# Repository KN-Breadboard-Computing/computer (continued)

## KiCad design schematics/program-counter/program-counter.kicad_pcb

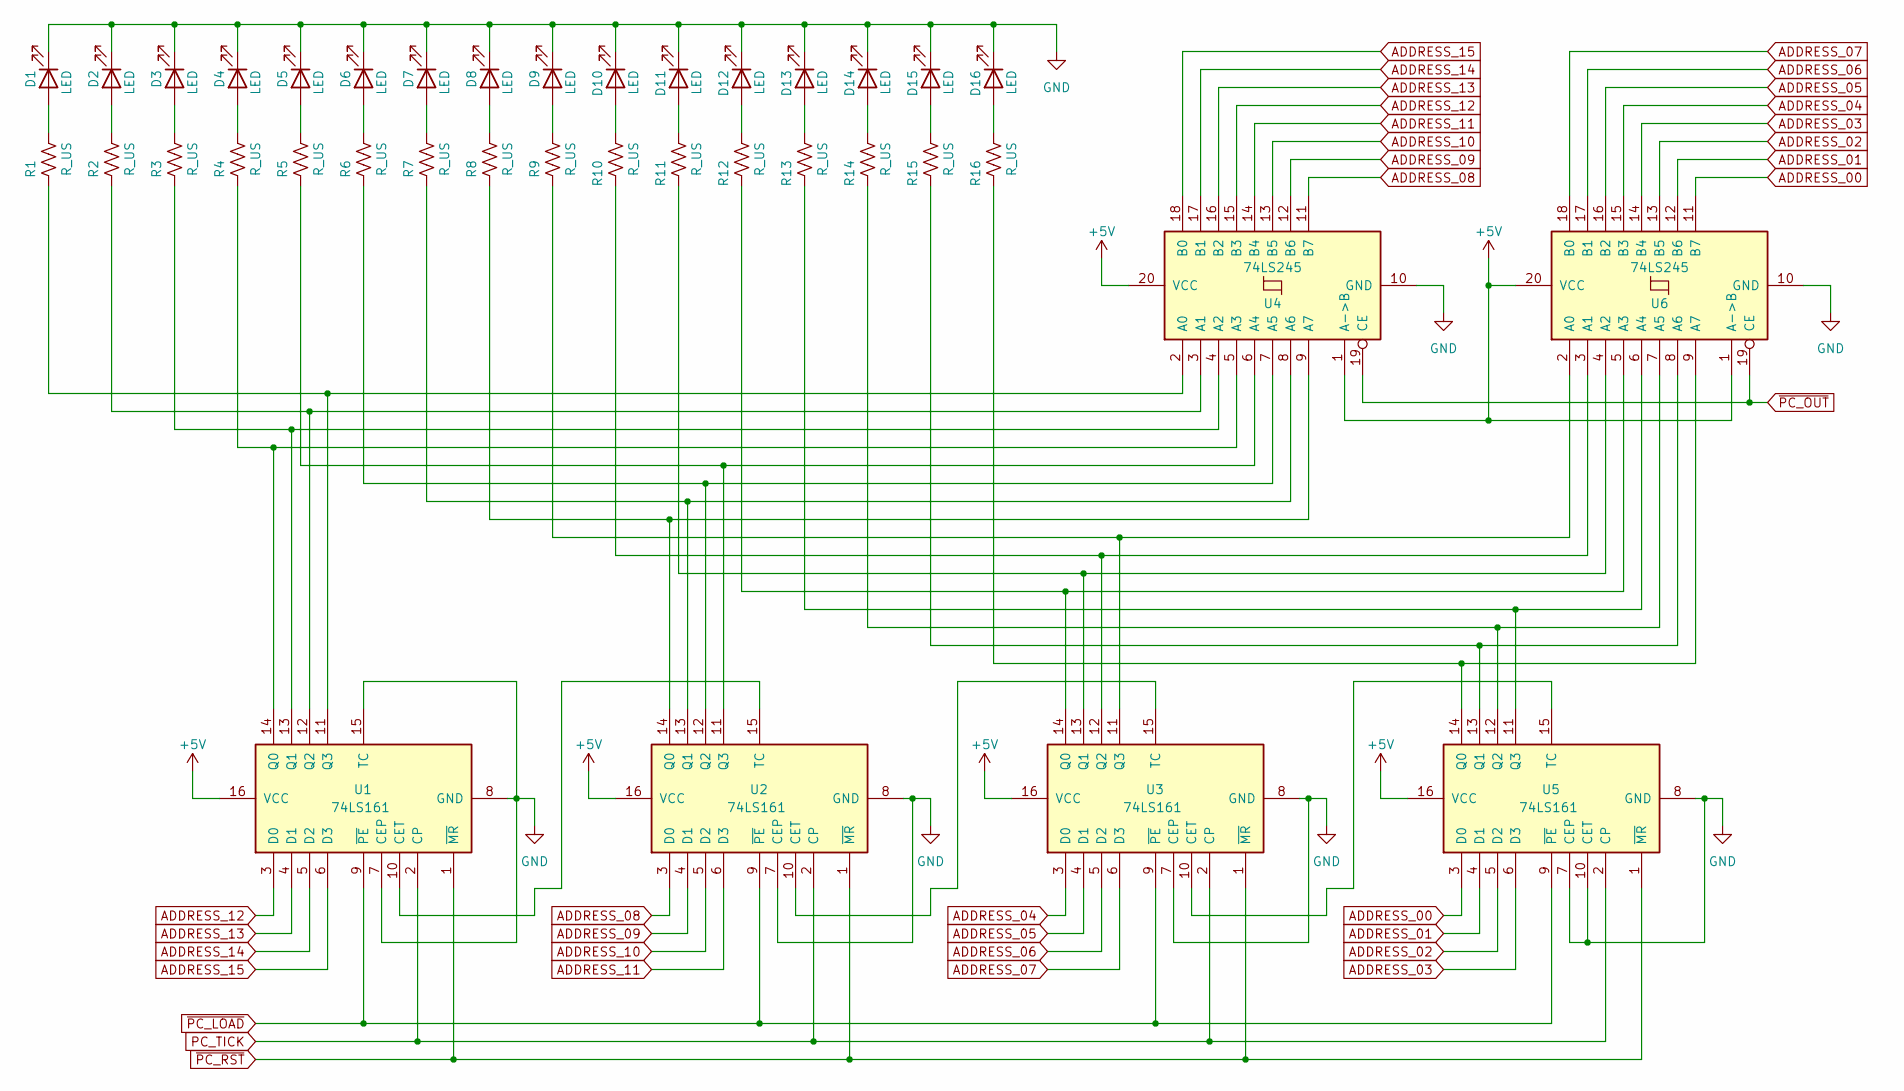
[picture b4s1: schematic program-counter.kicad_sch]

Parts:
D1, D2, D3, D4, D5, D6, D7, D8, D9, D10, D11, D12, D13, D14, D15, D16: LED; LED_D3.0mm
R1, R2, R3, R4, R5, R6, R7, R8, R9, R10, R11, R12, R13, R14, R15, R16: R_US; R_Axial_DIN0207_L6.3mm_D2.5mm_P10.16mm_Horizontal
U1, U2, U3, U5: 74LS161; DIP-16_W7.62mm_LongPads
U4, U6: 74LS245; DIP-20_W7.62mm_LongPads

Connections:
+5V: U1.16 (VCC), U2.16 (VCC), U3.16 (VCC), U4.1 (A->B), U4.20 (VCC), U5.16 (VCC), U6.1 (A->B), U6.20 (VCC)
ADDRESS_00: U5.3 (D0), U6.11 (B7)
ADDRESS_01: U5.4 (D1), U6.12 (B6)
ADDRESS_02: U5.5 (D2), U6.13 (B5)
ADDRESS_03: U5.6 (D3), U6.14 (B4)
ADDRESS_04: U3.3 (D0), U6.15 (B3)
ADDRESS_05: U3.4 (D1), U6.16 (B2)
ADDRESS_06: U3.5 (D2), U6.17 (B1)
ADDRESS_07: U3.6 (D3), U6.18 (B0)
ADDRESS_08: U2.3 (D0), U4.11 (B7)
ADDRESS_09: U2.4 (D1), U4.12 (B6)
ADDRESS_10: U2.5 (D2), U4.13 (B5)
ADDRESS_11: U2.6 (D3), U4.14 (B4)
ADDRESS_12: U1.3 (D0), U4.15 (B3)
ADDRESS_13: U1.4 (D1), U4.16 (B2)
ADDRESS_14: U1.5 (D2), U4.17 (B1)
ADDRESS_15: U1.6 (D3), U4.18 (B0)
GND: D1.1 (K), D2.1 (K), D3.1 (K), D4.1 (K), D5.1 (K), D6.1 (K), D7.1 (K), D8.1 (K), D9.1 (K), D10.1 (K), D11.1 (K), D12.1 (K), D13.1 (K), D14.1 (K), D15.1 (K), D16.1 (K), U1.7 (CEP), U1.8 (GND), U1.15 (TC), U2.7 (CEP), U2.8 (GND), U3.7 (CEP), U3.8 (GND), U4.10 (GND), U5.7 (CEP), U5.8 (GND), U5.10 (CET), U6.10 (GND)
unnamed: D1.2 (A), R1.2
unnamed: D2.2 (A), R2.2
unnamed: D3.2 (A), R3.2
unnamed: D4.2 (A), R4.2
unnamed: D5.2 (A), R5.2
unnamed: D6.2 (A), R6.2
unnamed: D7.2 (A), R7.2
unnamed: D8.2 (A), R8.2
unnamed: D9.2 (A), R9.2
unnamed: D10.2 (A), R10.2
unnamed: D11.2 (A), R11.2
unnamed: D12.2 (A), R12.2
unnamed: D13.2 (A), R13.2
unnamed: D14.2 (A), R14.2
unnamed: D15.2 (A), R15.2
unnamed: D16.2 (A), R16.2
unnamed: U1.10 (CET), U2.15 (TC)
unnamed: R4.1, U1.14 (Q0), U4.5 (A3)
unnamed: R3.1, U1.13 (Q1), U4.4 (A2)
unnamed: R2.1, U1.12 (Q2), U4.3 (A1)
unnamed: R1.1, U1.11 (Q3), U4.2 (A0)
unnamed: U2.10 (CET), U3.15 (TC)
unnamed: R8.1, U2.14 (Q0), U4.9 (A7)
unnamed: R7.1, U2.13 (Q1), U4.8 (A6)
unnamed: R6.1, U2.12 (Q2), U4.7 (A5)
unnamed: R5.1, U2.11 (Q3), U4.6 (A4)
unnamed: U3.10 (CET), U5.15 (TC)
unnamed: R12.1, U3.14 (Q0), U6.5 (A3)
unnamed: R11.1, U3.13 (Q1), U6.4 (A2)
unnamed: R10.1, U3.12 (Q2), U6.3 (A1)
unnamed: R9.1, U3.11 (Q3), U6.2 (A0)
unnamed: R16.1, U5.14 (Q0), U6.9 (A7)
unnamed: R15.1, U5.13 (Q1), U6.8 (A6)
unnamed: R14.1, U5.12 (Q2), U6.7 (A5)
unnamed: R13.1, U5.11 (Q3), U6.6 (A4)
PC_INC: U1.2 (CP), U2.2 (CP), U3.2 (CP), U5.2 (CP)
~PC_LOAD: U1.9 (~PE), U2.9 (~PE), U3.9 (~PE), U5.9 (~PE)
~PC_OUT: U4.19 (CE), U6.19 (CE)
~PC_RST: U1.1 (~MR), U2.1 (~MR), U3.1 (~MR), U5.1 (~MR)

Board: 2 copper layers, 38 parts (0 on the bottom side), 57 nets, no tracks yet.

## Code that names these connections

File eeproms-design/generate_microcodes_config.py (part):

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        }

    def _alu_operation(self, code):
        self._signals['~ALU_OUT'] = 0
        for i in range(0, 5):
            self._signals[f'ALU_OPC_{i}'] = (code >> i) & 0x1
    
    def no_mcc_tick(self):
        self._signals['MCC_TICK'] = 0
        return self 

    def mcc_rst(self):
        self._signals['MCC_RST'] = 1

    def reg_to_bus(self, reg):
        assert reg in WORD_REGS or reg == REG_F or reg == REG_INT
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            self._signals[f'~REG_{reg}_PASS_DATA'] = 0

        if reg == REG_F:
            self._signals['~REG_F_OUT'] = 0

        if reg == REG_INT:
            self._signals['~INT_DATA_OUT'] = 0
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        return self

    def pc_out(self):
        self._signals['~PC_OUT'] = 0
        return self

    def pc_in(self):
        self._signals['~PC_LOAD'] = 0
        return self

    def pc_inc(self):
        self._signals['PC_TICK'] = 1
        return self

    def mar_in(self):
        self._signals['REG_MAR_LOAD'] = 1
        return self

    def ir_in(self):
        self._signals['REG_IR_LOAD'] = 1
        return self

    def mbr_in(self):
        self._signals['REG_MBR_LOAD'] = 1
        self._signals['~REG_MBR_USE_BUS'] = 0
        self._signals['REG_MBR_WORD_DIR'] = 1
        return self

    def mem_to_bus(self, zero_page=False, stack=False):
        self._signals['REG_MBR_WORD_DIR'] = 0
        self._signals['~MEM_OUT'] = 0
        self._signals['~REG_MBR_USE_BUS'] = 0
        self._signals['~ZERO_PAGE'] = 0 if zero_page else 1
        self._signals['MEM_PART'] = 1 if stack else 0
        return self

    def mem_to_mbr(self, zero_page=False, stack=False):
        self._signals['REG_MBR_LOAD'] = 1
        self._signals['~MEM_OUT'] = 0
        self._signals['~ZERO_PAGE'] = 0 if zero_page else 1
        self._signals['MEM_PART'] = 1 if stack else 0
        return self

    def mbr_to_mem(self, zero_page=False, stack=False):
        self._signals['~MEM_IN'] = 0
        self._signals['~ZERO_PAGE'] = 0 if zero_page else 1
        self._signals['MEM_PART'] = 1 if stack else 0
        return self
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            self._signals[f'REG_{dst}_LOAD'] = 1

            if dst == REG_MBR:
                self._signals['~REG_MBR_USE_BUS'] = 0

        return self

    def tmp_out(self):
        self._signals['~REG_TMPH_OUT'] = 0
        self._signals['~REG_TMPL_OUT'] = 0
        self._signals['REG_TMP_ADDRESS_DIR'] = 0
        self._signals['~REG_TMP_PASS_ADDRESS'] = 0
        return self

    def tmp_in(self):
        return self.reg_from_bus(REG_TL).reg_from_bus(REG_TH)

    def tmp_addr_in(self):
        self._signals['REG_TMPH_LOAD'] = 1
        self._signals['REG_TMPL_LOAD'] = 1
        self._signals['REG_TMP_ADDRESS_DIR'] = 1
        self._signals['~REG_TMP_PASS_ADDRESS'] = 0
        return self

    def stc_out(self):
        self._signals['~STC_OUT'] = 0
        return self

    def stc_dec(self):
        self._signals['STC_TICK'] = 1
        return self

    def stc_inc(self):
        self._signals['STC_TICK'] = 1
        self._signals['STC_MODE'] = 1
        return self

    def set_int_enable(self):
        self._signals['SET_INT_ENABLE'] = 1
        return self

    def rst_int_enable(self):
        self._signals['RST_INT_ENABLE'] = 1
        return self

    def int_addr_out(self):
        self._signals['~INT_ADDRESS_OUT'] = 1
        return self
    
    def int_data_out(self):
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        return self
    
    def select_boot_memory(self):
        self._signals['MEMORY_SELECTOR'] = 0
        return self

    def to_json(self):
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
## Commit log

2022-12-15 Created program counter project in logisim
2023-01-30 Added notes
2023-01-30 Changes to noets
2023-02-27 Programming EEPROMs - first version of signals
2023-04-07 Changes in eeproms code
2023-04-09 Deleted old and useless files
2023-04-09 Initial schematic projects
2023-07-06 Created almost all schematics
2023-07-06 Arduino code updates
2023-07-06 ReadMe update
2023-07-31 Directories refactor
2023-07-31 Script for eeproms programming. Implemented alu logic eeprom
2023-07-31 Named signal masks
2023-07-31 Base of architecture manual and arduino memory writer
2023-07-31 Corrected ALU schematic after diy pcb soldered
2023-07-31 Described flags
2023-07-31 Photo report - stage 1
2023-08-18 Implemented bus control
2023-08-21 Corrections after second diy pcb soldered
2023-08-22 Code for eeproms with basic instruction decoding
2023-08-22 Deleted pycache
2023-08-25 Control unit build
2023-10-04 Implemented signals visualization
2023-10-10 Changed signals visualisation
2023-10-24 New instructions tested
2023-11-20 Manual -> github pages
2023-11-26 Repo structure refactor
2023-11-26 Move instructions
2023-11-26 Created script for generating alu config
2023-11-27 Alu instructions
2023-12-12 Created a basic verilog project structure
2023-12-18 Renamed the verilog-project/ dir to verilog/
2023-12-18 Updated CMakeLists, integrated ctest
2023-12-18 Removed the temporary ALU, added a tristate buffer
2023-12-18 Signal definitions
2023-12-18 Created skeleton files for alu, cpu and control unit
2023-12-18 Added register
2023-12-18 Counter
2023-12-18 Added RAM (broken)
2023-12-18 Counter fix and more cpu
2023-12-18 Added a newline!
2023-12-18 Fixed cmake
2023-12-18 Fixed commas
2023-12-18 Created base for ALU
2023-12-19 Fixed alu, added tests for alu, added fixmes to ram
2023-12-19 Added examples
2023-12-19 Tests for counter
2023-12-19 ALU in CPU and changed parameter declarations
2023-12-20 Update instructions.json
    added missing HALT instruction
2023-12-21 Instructions have been completed
2023-12-21 Instruction json formatted
2023-12-21 Removed MUL2 operation
2024-01-15 Update generate_instructions_config.py
    naprawione
2024-01-15 Generated fresh config
2024-01-20 Added "depend-on-flag" field to instructions config and generated new one.
2024-02-13 [verilog] Fixed RAM, added Memory Unit
    - Write to RAM is triggered by write_enable going low, or a change in
    address (write_enable has to still be low). Changes in data, however,
    do not trigger anything
    - In Mem Unit MAR and MBR only store a new value on the rising edge of
    their respective signals. This means that 2 consecutive commands to
    load MAR/MBR will not work unless there is a assertion of thier load
2024-02-14 Rewritten tests for ALU, added .clang-format
2024-02-14 Added logging to ALU tests
2024-02-20 Made Control Unit process basic instructions
    - The ROM file generation that Control Unit needs to work is not
    included
    - Conditionals do not work
2024-02-22 Added microcodes generator
    - Only includes microcodes present in existing `config/microcodes.json`
    and `config/instructions.json`
    - There are some differences between hand written config and one
    generated by this script
    - Due to previous 2 points generated config is not included in this
    commit
2024-02-23 Added missing microcodes to the generator
    - Now all microcodes present in the `config/instructions.json` are
    generated
    - Increment and decrement microcodes are noops for now, due to lack of
    support in the ALU config (at least)
2024-02-24 Fixed EEPROM import and config paths
    - At least on my machine when run from `eeprom-design` directory
    everything is now imported properly
    - Config file paths are no longer hardcoded and can be now provided by
    users of EEPROM classes
2024-02-24 Added dump_eeproms.py utility
    - It generates and dumps the contents of EEPROMs into binary files
2024-02-26 Fixed stack related issues in microcode generator
    - Some microcodes that should have operated on the stack, did not
2024-02-26 Added more elaborate Control Unit tests
    - Now more instructions are tested
    - Probably all of them should be tested
    - And, too be fair hardcoding microdes into tests might not have been
    the smartest of ideas
2024-03-02 Added `branch` to instruction config
    - `branch.taken` - instruction that is executed if the branch is taken
    - `branch.not-taken` - instruction that is executed otherwise
2024-03-03 Added branch decoding EEPROM
2024-03-03 Added branches to Control Unit
    - Control Unit can now change its output depending on ALU flags and
    implement branching (via JMP and SKIP instructions)
2024-03-08 Added base for windowing using raylib
2024-03-08 Rewrote ALU, added ALU flags
    - Flags now work correctly
    - ALU more closely resembles its breadboard counterpart
    - Removed clock input (now it's mostly combinatorial logic)
2024-03-08 Added initial version of GPU verilator component
2024-03-09 Updated the simulator code to include a set_pixel function
2024-03-09 Changed the cursors in GPU to point to glyphs instead of individual pixels
2024-03-10 Added proof of concept GPU to the raylib simulation
2024-03-10 Added vertical and horizontal counters
2024-03-18 Added INT signals
    - Currently hard wired to 0, support from EEPROMs is needed to actually
    do something useful
2024-03-18 Added the TMP register
2024-04-02 Added glyph and color buffers to the GPU
2024-04-03 Font loading part 1
2024-04-03 Added a tool that converts a font image file to a binary accepted by the GPU
2024-04-03 Fixed the simulator, the GPU is still broken
2024-04-03 Added error handling if the GPU fails to open the Glyph data file
2024-04-04 Added a shift register module
2024-04-06 GPU now correctly loads the file, still displays nonsense though
2024-04-06 Changed the test for shift reg
2024-04-07 Working CPU
    - CPU now works, at least to pass a simple MOV-only test
2024-04-10 Added missing `cpu_adapter.sv`
2024-04-10 Added missing files
2024-04-10 Debug version of the simulator
2024-04-17 Made GPU render test graphics correctly
    - It now renders simple graphics in fonts/
    - I did not want to push this code, which I believe is very cursed
2024-04-18 Added modcounter
2024-04-18 Added tests for modcounter
2024-04-18 Moved resources to resources directory
2024-04-23 Added Clock wrapper and a scheduler to the simulator
2024-04-23 added ps2 keyboard raylib wrapper.
2024-04-23 fixed formatting.
2024-04-24 Added negative edge period to the clock and option to start from posedge, added missing imports to ps2.hpp
2024-04-29 Schematics and interrupts
2024-04-30 Diy pbcs photos
2024-05-03 Made CPU jump to ISR
    - Return from ISR does not work yet
2024-05-05 Improved details
2024-05-08 Added Set-Reset Latch
2024-05-08 Changed assert to be correct in struct Clock
2024-05-08 Fixed off by one problem in GPU
2024-05-08 Instructions moving interrupt data
2024-05-08 Int enable set/reset swapped
2024-05-09 Added full font
2024-05-14 Addded instructions triggering interrupts
2024-05-14 Sanitized the ps2 implementation
2024-05-14 GPU interrupts part 1 (debugging functionality)
2024-05-14 GPU interrupts part 2 (working set_glyph, off by one display)
2024-05-15 Added imgui for simulator debugging
2024-05-15 Added imterm and raylib 5.0 fetching
2024-05-15 Fixed cursed cmake not linking raylib to imgui
2024-05-19 PCBs done
2024-05-23 Generated gerber files
2024-10-17 [GPU] Added reset, colors are now rendered
    - Rendering is still broken, due to shift_reg not shifting afert
    loading for 1 cycle, thus the first column of a glyph is rendered
    twice
    - This might not be the only problem
2025-01-20 Config update
2025-01-26 Instructions (function call and return) update
2025-01-28 Math mode generation correction
2025-02-21 New instructions - move values indirectly from memory to registers
2025-03-19 Removed testbenches directory, removed $monitor statements that threw compiling errors
2025-07-11 Zero page handling
